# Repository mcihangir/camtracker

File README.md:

# SmartNFC

## Description
**SmartNFC** is an Android Virtual POS Application designed to operate on Android 13/14.

## Project Information
- **Project Name**: SmartNFC
- **Description**: Android Virtual POS Application
- **Start Date**: 2024-06-17
- **Firmware/SDK Version**: Android 13/14
- **Hardware Version**: v1.0

## Folder Structure
The project follows the directory structure outlined below:

```
SmartNFC/
│-- Block Diagrams/        # Product Block Diagram, PCB Connector Position
│-- Product Tree/          # Product Tree
│-- Documents/             # Design Documents, User Manuals, etc.
│-- Hardware/              # PCB Design Sources and libraries
│-- Software/              # Firmware and Applications
│-- Tools/                 # Software Tools
│-- Data/                  # Manufacturing data (PCB Gerber, Firmware Images, etc.)
```

## Folder Descriptions
- **Block Diagrams/**: Contains product-level block diagrams and PCB connector positioning.
- **Product Tree/**: Hierarchical structure of the product components.
- **Documents/**: Includes all necessary datasheets related to the hardware components and design documents.
- **Hardware/**: Contains PCB design source files and libraries.
- **Software/**: Includes firmware and application source code.
- **Tools/**: Collection of software tools required for development and debugging.
- **Data/**: Stores manufacturing data, including PCB Gerber files and firmware images.

## License
TBD

## Contact
For more details, reach out to the development team.

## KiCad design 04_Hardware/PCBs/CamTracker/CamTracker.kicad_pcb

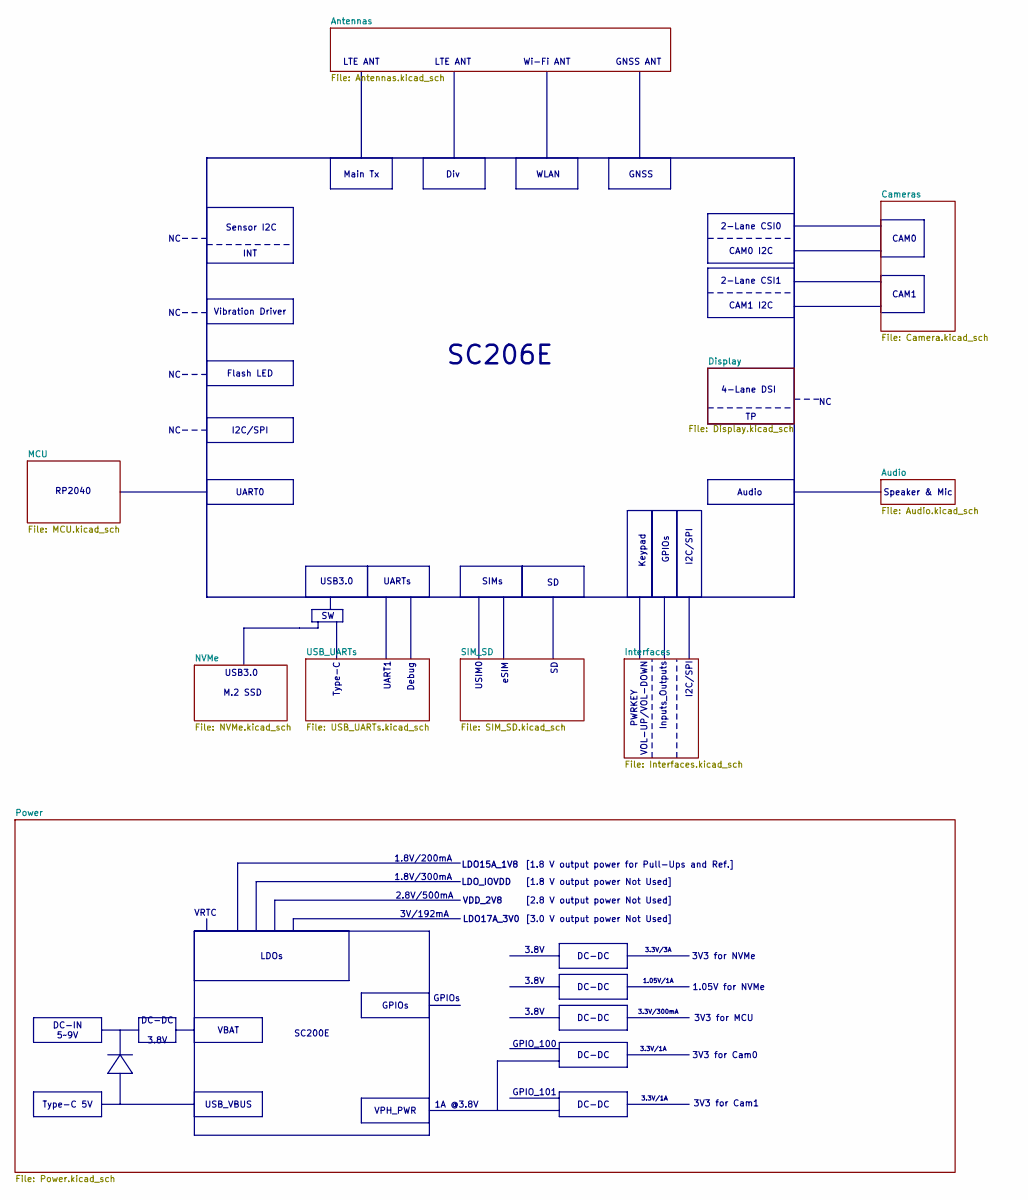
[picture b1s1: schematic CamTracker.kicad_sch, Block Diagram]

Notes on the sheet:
PWRKEY VOL-UP/VOL-DOWN
3V3 for MCU
LDO17A_3V0
UARTs
1.05V for NVMe
Debug
GPIOs
I2C/SPI
Inputs_Outputs
USIM0
3.8V
CAM1
[1.8 V output power Not Used]
[3.0 V output power Not Used]
RP2040
1.8V/300mA
1.05V/1A
4-Lane DSI
VRTC
3.3V/1A
3V3 for NVMe
3.8V
USB3.0
SC206E
1A @3.8V
Type-C
CAM0
eSIM
2.8V/500mA
Vibration Driver
3.3V/300mA
2-Lane CSI1
Main Tx
Speaker & Mic
3V3 for Cam0
M.2 SSD
GNSS
VDD_2V8
2-Lane CSI0
CAM1 I2C

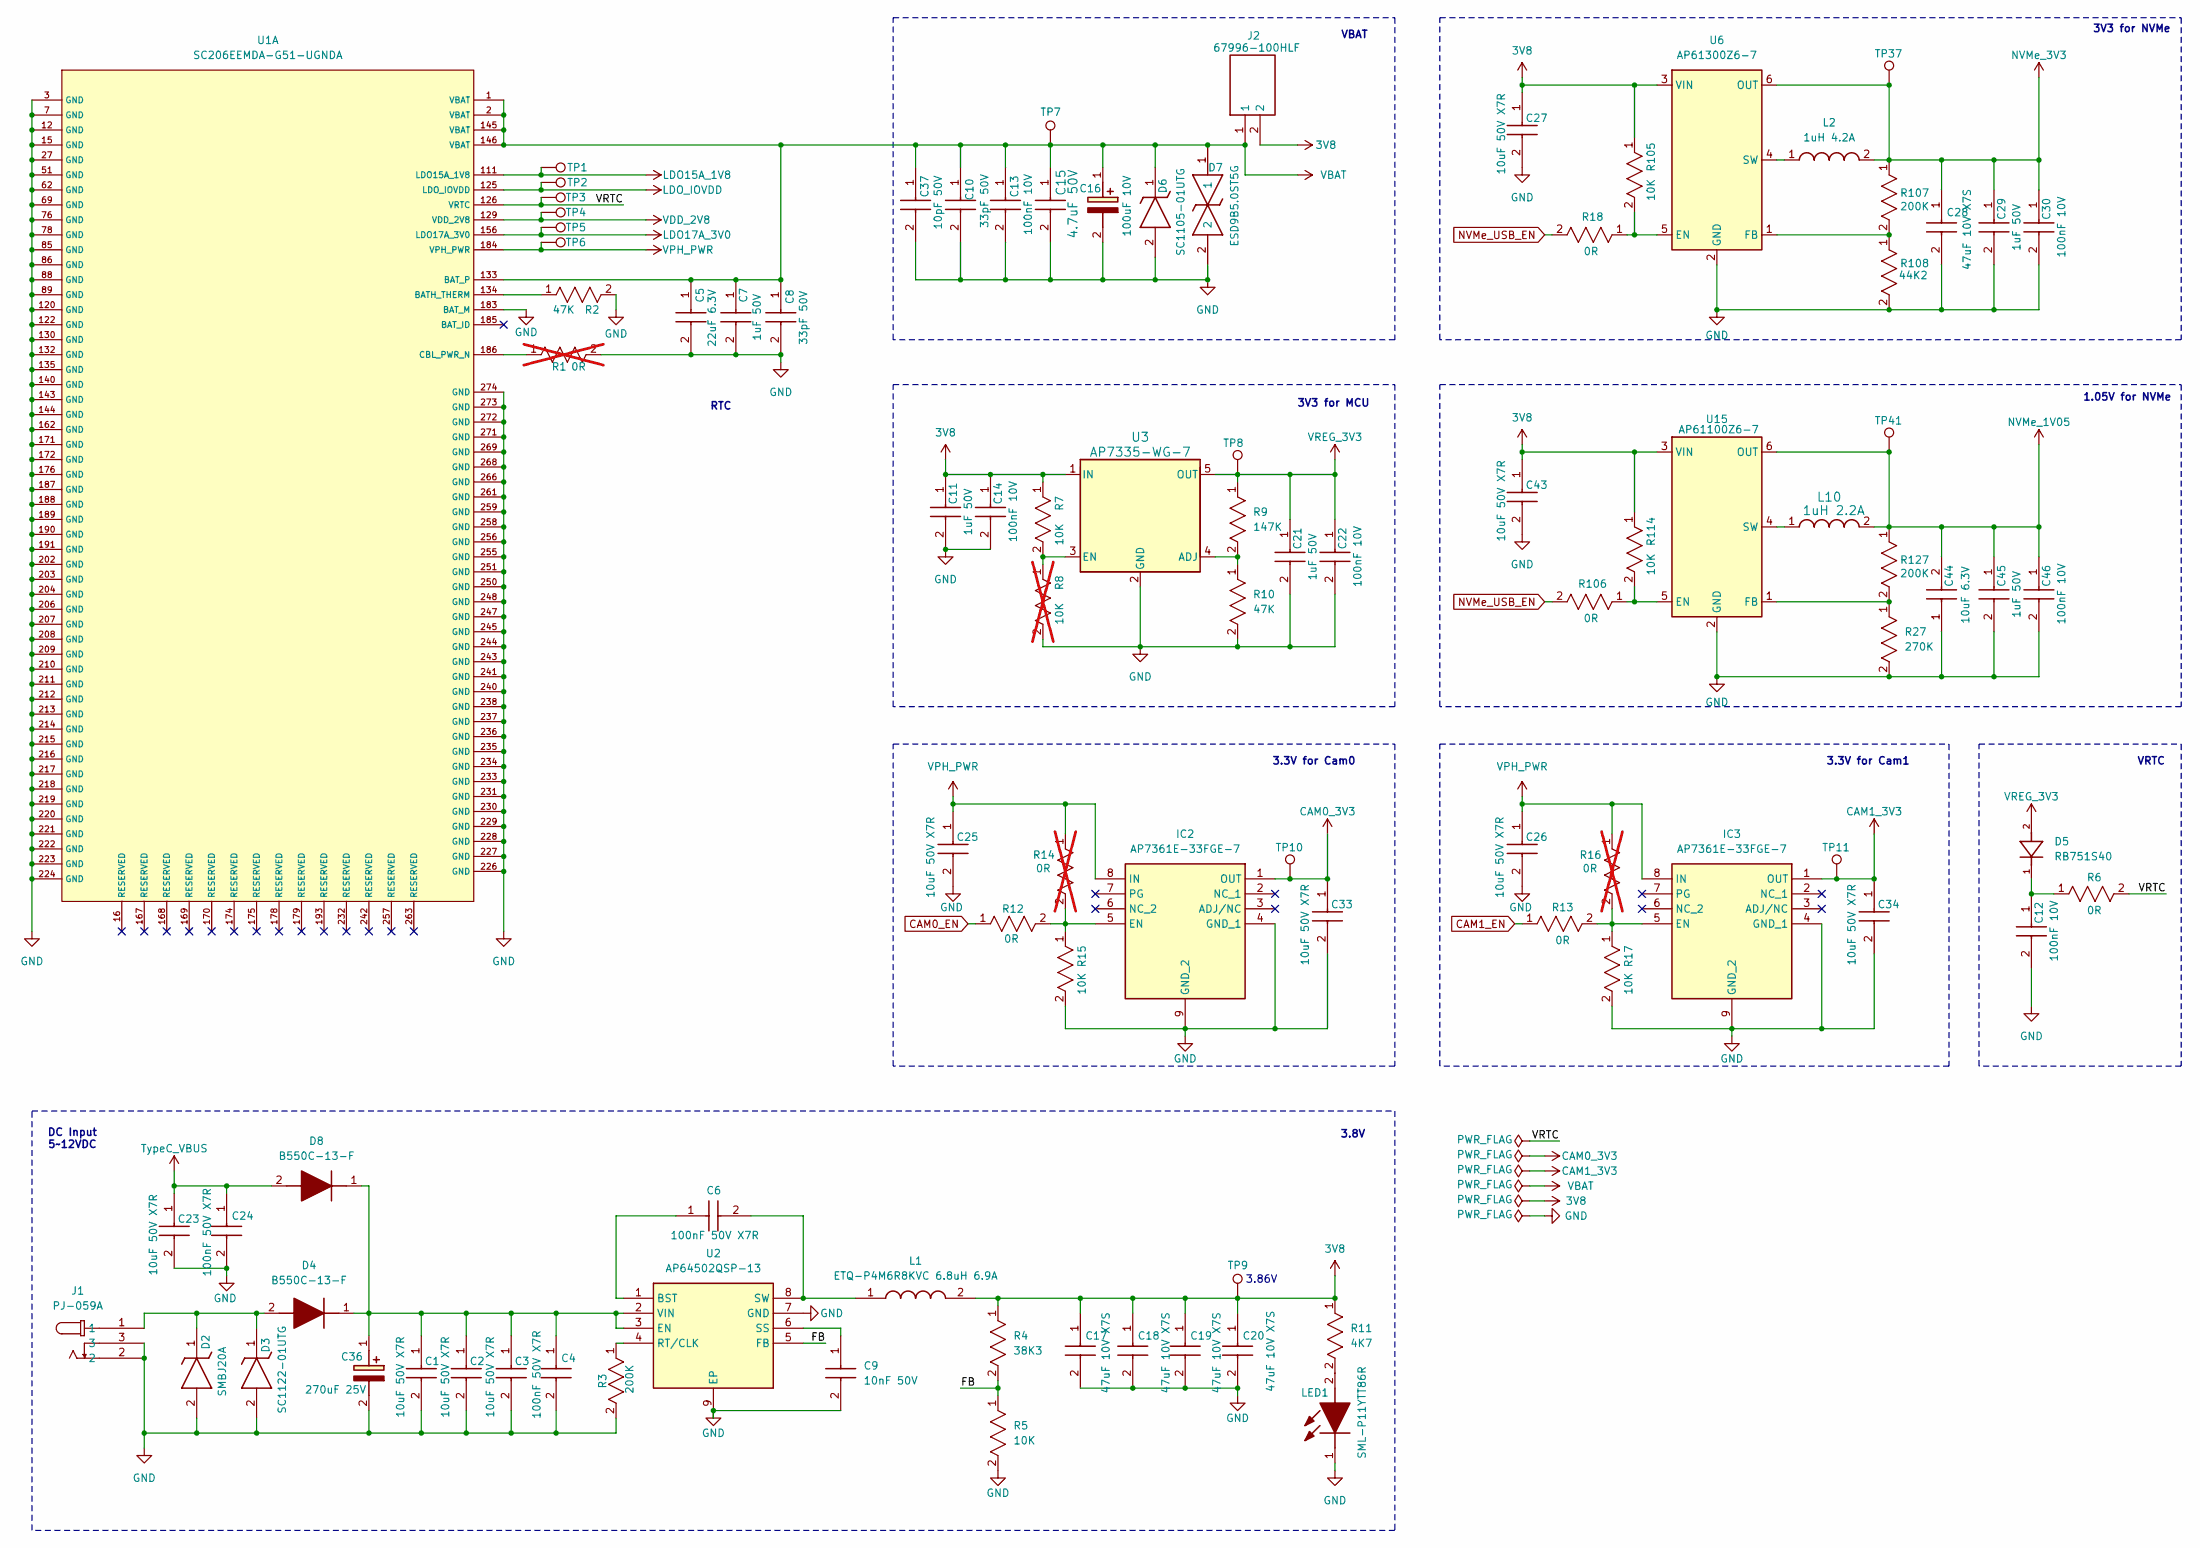
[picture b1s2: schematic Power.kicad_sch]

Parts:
C1, C2, C3, C23, C25, C26, C27, C33, C34, C43: 10uF 50V X7R; CAPC3216X190N; Part Number CL31B106KBK6PJE
C4, C6, C24: 100nF 50V X7R; CAPC1005X55N; Part Number UMK105B7104KVHF
C5: 22uF 6.3V; CAPC1005X55N; Part Number GRM158R60J226ME01D
C7, C11, C21, C29, C45: 1uF 50V; CAPC1005X55N; Part Number GRM155R61H105KE05D
C8, C10: 33pF 50V; CAPC1005X55N; Part Number GRM1555C1H330JA01D
C9: 10nF 50V; CAPC1005X55N; Part Number GRM155R71H103KA88D
C12, C13, C14, C22, C30, C46: 100nF 10V; CAPC1005X55N; Part Number GRM155R71A104KA01D
C15: 4.7uF 50V; CAP_UMK325B7475MM-T_TAY; Part Number UMK325BJ475MM-T
C16: 100uF 10V; T495D; Part Number T495D107K010ATE080
C17, C18, C19, C20, C28: 47uF 10V X7S; CAPC3225X280N; Part Number CGA6P1X7S1A476M250AC
C36: 270uF 25V; 16SVPT560M; Part Number 25SVPG270M
C37: 10pF 50V; CAPC1005X55N; Part Number GRM1555C1H100JA01D
C44: 10uF 6.3V; CAPC1005X55N; Part Number GRM155R60J106ME15D
D2: SMBJ20A; DIOM5436X244N; Part Number SMBJ20A
D3: SC1122-01UTG; SC110501UTG; Part Number SC1122-01UTG
D4, D8: B550C-13-F; DIOM7959X250N; Part Number B550C-13-F
D5: RB751S40; SOD1608X70; Part Number RB751S40
D6: SC1105-01UTG; SC110501UTG; Part Number SC1105-01UTG
D7: ESD9B5.0ST5G; SODFL1006X40N; Part Number ESD9B5.0ST5G
IC2, IC3: AP7361E-33FGE-7; SON65P300X300X63-9N; Part Number AP7361E-33FGE-7
J1: PJ-059A; PJ059A; Part Number PJ-059A
J2: 67996-100HLF; HDRV2W67P254_2X1_254X483X858P; Part Number 67996-100HLF
L1: ETQ-P4M6R8KVC 6.8uH 6.9A; ETQ-P4M_KVC; Part Number ETQ-P4M6R8KVC
L2: 1uH 4.2A; LSEUC3225HKT1R0M; Part Number LSEUC3225HKT1R0M
L10: 1uH 2.2A; IND_WE-LQS_2512_WRE; Part Number 74404024010
LED1: SML-P11YTT86R; SMLP11VTT86R; Part Number SML-P11YTT86R
R1: 0R; RC0402N_YAG; Part Number RC0402JR-070RL; not fitted
R2, R10: 47K; RC0402N_YAG; Part Number RC0402JR-0747KL
R3, R107, R127: 200K; RC0402N_YAG; Part Number RC0402FR-07200KL
R4: 38K3; RC0402N_YAG; Part Number AF0402FR-0738K3L
R5, R7, R15, R17, R105, R114: 10K; RC0402N_YAG; Part Number RC0402JR-0710KL
R6, R12, R13: 0R; RESC2012X50N; Part Number CRCW08050000Z0EA
R8: 10K; RC0402N_YAG; Part Number RC0402JR-0710KL; not fitted
R9: 147K; RC0402N_YAG; Part Number RC0402FR-07147KL
R11: 4K7; RC0402N_YAG; Part Number RC0402JR-074K7L
R14, R16: 0R; RESC2012X50N; Part Number CRCW08050000Z0EA; not fitted
R18, R106: 0R; RC0402N_YAG; Part Number RC0402JR-070RL
R27: 270K; RC0402N_YAG; Part Number RC0402FR-07270KL
R108: 44K2; RC0402N_YAG; Part Number RC0402FR-0744K2L
TP1, TP2, TP3, TP4, TP5, TP6, TP7, TP8, TP10, TP11, TP37, TP41: TestPoint; TestPoint_Pad_D1.0mm
TP9: 3.86V; TestPoint_Pad_D1.0mm
U1: SC206EEMDA-G51-UGNDA; SC200E_SC206E; Part Number SC200EEMNA-E53-UGNDA
U2: AP64502QSP-13; SOIC127P600X163-9N; Part Number AP64502QSP-13
U3: AP7335-WG-7; SOT95P285X145-5N; Part Number AP7335-WG-7
U6: AP61300Z6-7; SOT50P162X60-6N; Part Number AP61100Z6-7
U15: AP61100Z6-7; SOT50P162X60-6N; Part Number AP61100Z6-7

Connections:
3V8: C11.1, C14.1, C17.1, C18.1, C19.1, C20.1, C27.1, C43.1, J2.2, L1.2, R4.1, R7.1, R11.1, R105.1, R114.1, TP9.1, U3.1 (IN), U6.3 (VIN), U15.3 (VIN); also elsewhere on the board
/Power/FB: R4.2, R5.1, U2.5 (FB)
/Power/VRTC: R6.2, TP3.1, U1.126 (VRTC)
CAM0_3V3: C33.1, IC2.1 (OUT), TP10.1; also elsewhere on the board
CAM0_EN: R12.1; also elsewhere on the board
CAM1_3V3: C34.1, IC3.1 (OUT), TP11.1; also elsewhere on the board
CAM1_EN: R13.1; also elsewhere on the board
GND: C1.2, C2.2, C3.2, C4.2, C5.2, C7.2, C8.2, C9.2, C10.2, C11.2, C12.2, C13.2, C14.2, C15.2, C16.2 (-), C17.2, C18.2, C19.2, C20.2, C21.2, C22.2, C23.2, C24.2, C25.2, C26.2, C27.2, C28.2, C29.2, C30.2, C33.2, C34.2, C36.2 (-), C37.2, C43.2, C44.1, C45.2, C46.2, D2.2 (A), D3.2 (A), D6.2 (A), D7.2, IC2.4 (GND_1), IC2.9 (GND_2), IC3.4 (GND_1), IC3.9 (GND_2), J1.2, J1.3, LED1.1 (K), R1.2, R2.2, R3.2, R5.2, R8.2, R10.2, R15.2, R17.2, R27.2, R108.2, U1.3 (GND), U1.7 (GND), U1.12 (GND), U1.15 (GND), U1.27 (GND), U1.51 (GND), U1.62 (GND), U1.69 (GND), U1.76 (GND), U1.78 (GND), U1.85 (GND), U1.86 (GND), U1.88 (GND), U1.89 (GND), U1.120 (GND), U1.122 (GND), U1.130 (GND), U1.132 (GND), U1.135 (GND), U1.140 (GND), U1.143 (GND), U1.144 (GND), U1.162 (GND), U1.171 (GND), U1.172 (GND), U1.176 (GND), U1.183 (BAT_M), U1.187 (GND), U1.188 (GND), U1.189 (GND), U1.190 (GND), U1.191 (GND), U1.202 (GND), U1.203 (GND), U1.204 (GND), U1.206 (GND), U1.207 (GND), U1.208 (GND), U1.209 (GND), U1.210 (GND), U1.211 (GND), U1.212 (GND), U1.213 (GND), U1.214 (GND), U1.215 (GND), U1.216 (GND), U1.217 (GND), U1.218 (GND), U1.219 (GND), U1.220 (GND), U1.221 (GND), U1.222 (GND), U1.223 (GND), U1.224 (GND), U1.226 (GND), U1.227 (GND), U1.228 (GND), U1.229 (GND), U1.230 (GND), U1.231 (GND), U1.233 (GND), U1.234 (GND), U1.235 (GND), U1.236 (GND), U1.237 (GND), U1.238 (GND), U1.240 (GND), U1.241 (GND), U1.243 (GND), U1.244 (GND), U1.245 (GND), U1.247 (GND), U1.248 (GND), U1.250 (GND), U1.251 (GND), U1.255 (GND), U1.256 (GND), U1.258 (GND), U1.259 (GND), U1.261 (GND), U1.266 (GND), U1.268 (GND), U1.269 (GND), U1.271 (GND), U1.272 (GND), U1.273 (GND), U1.274 (GND), U2.7 (GND), U2.9 (EP), U3.2 (GND), U6.2 (GND), U15.2 (GND); also elsewhere on the board
LDO15A_1V8: TP1.1, U1.111 (LDO15A_1V8); also elsewhere on the board
LDO17A_3V0: TP5.1, U1.156 (LDO17A_3V0)
LDO_IOVDD: TP2.1, U1.125 (LDO_IOVDD)
NVMe_1V05: C44.2, C45.1, C46.1, L10.2, R127.1, TP41.1, U15.6 (OUT); also elsewhere on the board
NVMe_3V3: C28.1, C29.1, C30.1, L2.2, R107.1, TP37.1, U6.6 (OUT); also elsewhere on the board
NVMe_USB_EN: R18.2, R106.2; also elsewhere on the board
unnamed: C12.1, D5.1, R6.1
unnamed: C1.1, C2.1, C3.1, C4.1, C36.1 (+), D4.1 (K), D8.1 (K), U2.2 (VIN), U2.3 (EN)
unnamed: D2.1 (K), D3.1 (K), D4.2 (A), J1.1
unnamed: IC2.5 (EN), R12.2, R14.2, R15.1
unnamed: IC3.5 (EN), R13.2, R16.2, R17.1
unnamed: LED1.2 (A), R11.2
unnamed: R2.1, U1.134 (BATH_THERM)
unnamed: R1.1, U1.186 (CBL_PWR_N)
unnamed: C6.1, U2.1 (BST)
unnamed: R3.1, U2.4 (RT/CLK)
unnamed: C9.1, U2.6 (SS)
unnamed: C6.2, L1.1, U2.8 (SW)
unnamed: R9.2, R10.1, U3.4 (ADJ)
unnamed: R7.2, R8.1, U3.3 (EN)
unnamed: R18.1, R105.2, U6.5 (EN)
unnamed: R107.2, R108.1, U6.1 (FB)
unnamed: L2.1, U6.4 (SW)
unnamed: R106.1, R114.2, U15.5 (EN)
unnamed: R27.1, R127.2, U15.1 (FB)
unnamed: L10.1, U15.4 (SW)
TypeC_VBUS: C23.1, C24.1, D8.2 (A); also elsewhere on the board
VBAT: C5.1, C7.1, C8.1, C10.1, C13.1, C15.1, C16.1 (+), C37.1, D6.1 (K), D7.1, J2.1, TP7.1, U1.1 (VBAT), U1.2 (VBAT), U1.133 (BAT_P), U1.145 (VBAT), U1.146 (VBAT); also elsewhere on the board
VDD_2V8: TP4.1, U1.129 (VDD_2V8)
VPH_PWR: C25.1, C26.1, IC2.8 (IN), IC3.8 (IN), R14.1, R16.1, TP6.1, U1.184 (VPH_PWR); also elsewhere on the board
VREG_3V3: C21.1, C22.1, D5.2, R9.1, TP8.1, U3.5 (OUT); also elsewhere on the board

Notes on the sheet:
3.3V for Cam0
VBAT
1.05V for NVMe
3V3 for NVMe
3V3 for MCU
RTC
3.8V
DC Input 5~12VDC
3.3V for Cam1
3.86V
VRTC

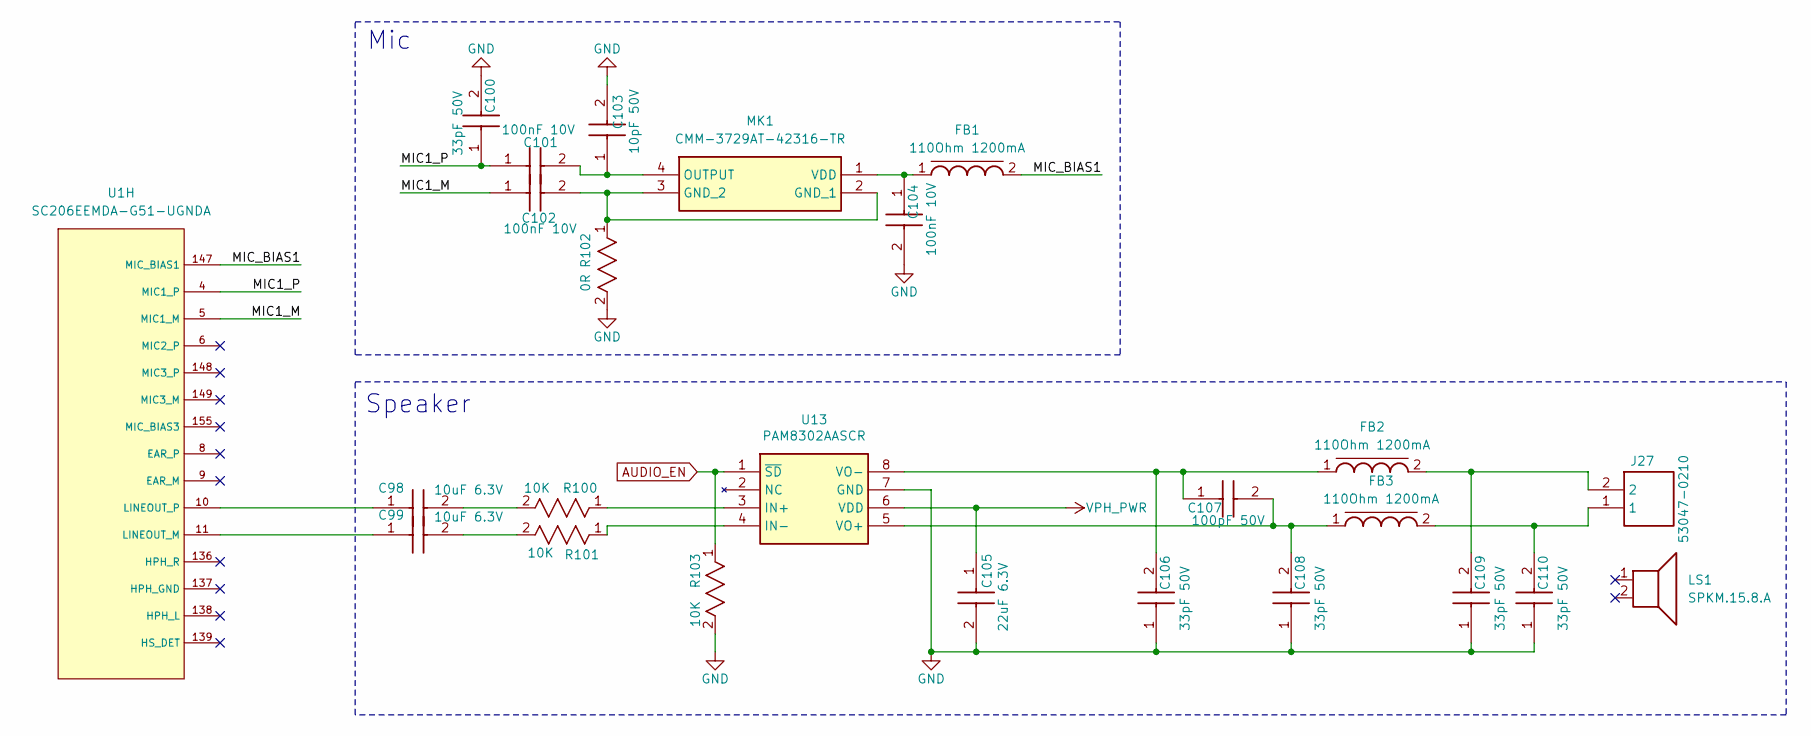
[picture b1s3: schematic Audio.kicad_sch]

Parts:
C98, C99: 10uF 6.3V; CAPC1005X55N; Part Number GRM155R60J106ME15D
C100, C106, C108, C109, C110: 33pF 50V; CAPC1005X55N; Part Number GRM1555C1H330JA01D
C101, C102, C104: 100nF 10V; CAPC1005X55N; Part Number GRM155R71A104KA01D
C103: 10pF 50V; CAPC1005X55N; Part Number GRM1555C1H100JA01D
C105: 22uF 6.3V; CAPC1005X55N; Part Number GRM158R60J226ME01D
C107: 100pF 50V; CAPC1005X55N; Part Number GRM1555C1H101JA01J
FB1, FB2, FB3: 110Ohm 1200mA; BEADC1005X55N; Part Number 74269242111
J27: 53047-0210; 530470210; Part Number 53047-0210
LS1: SPKM.15.8.A; Part Number SPKM.15.8.A
MK1: CMM-3729AT-42316-TR; CMM3729AT42316TR; Part Number CMM-3729AT-42316-TR
R100, R101, R103: 10K; RC0402N_YAG; Part Number RC0402JR-0710KL
R102: 0R; RC0402N_YAG; Part Number RC0402JR-070RL
U1: SC206EEMDA-G51-UGNDA; SC200E_SC206E; Part Number SC200EEMNA-E53-UGNDA
U13: PAM8302AASCR; SOP65P490X110-8N; Part Number PAM8302AASCR

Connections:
/Audio/MIC1_M: C102.1, U1.5 (MIC1_M)
/Audio/MIC1_P: C100.1, C101.1, U1.4 (MIC1_P)
/Audio/MIC_BIAS1: FB1.2, U1.147 (MIC_BIAS1)
AUDIO_EN: R103.1, U13.1 (~SD); also elsewhere on the board
GND: C100.2, C103.2, C104.2, C105.2, C106.1, C108.1, C109.1, C110.1, R102.2, R103.2, U13.7 (GND); also elsewhere on the board
unnamed: C98.2, R100.2
unnamed: C99.2, R101.2
unnamed: C109.2, FB2.2, J27.2
unnamed: C110.2, FB3.2, J27.1
unnamed: C102.2, MK1.2 (GND_1), MK1.3 (GND_2), R102.1
unnamed: C101.2, C103.1, MK1.4 (OUTPUT)
unnamed: C104.1, FB1.1, MK1.1 (VDD)
unnamed: C99.1, U1.11 (LINEOUT_M)
unnamed: C98.1, U1.10 (LINEOUT_P)
unnamed: R100.1, U13.3 (IN+)
unnamed: R101.1, U13.4 (IN-)
unnamed: C107.2, C108.2, FB3.1, U13.5 (VO+)
unnamed: C106.2, C107.1, FB2.1, U13.8 (VO-)
VPH_PWR: C105.1, U13.6 (VDD); also elsewhere on the board

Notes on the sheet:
Mic
Speaker

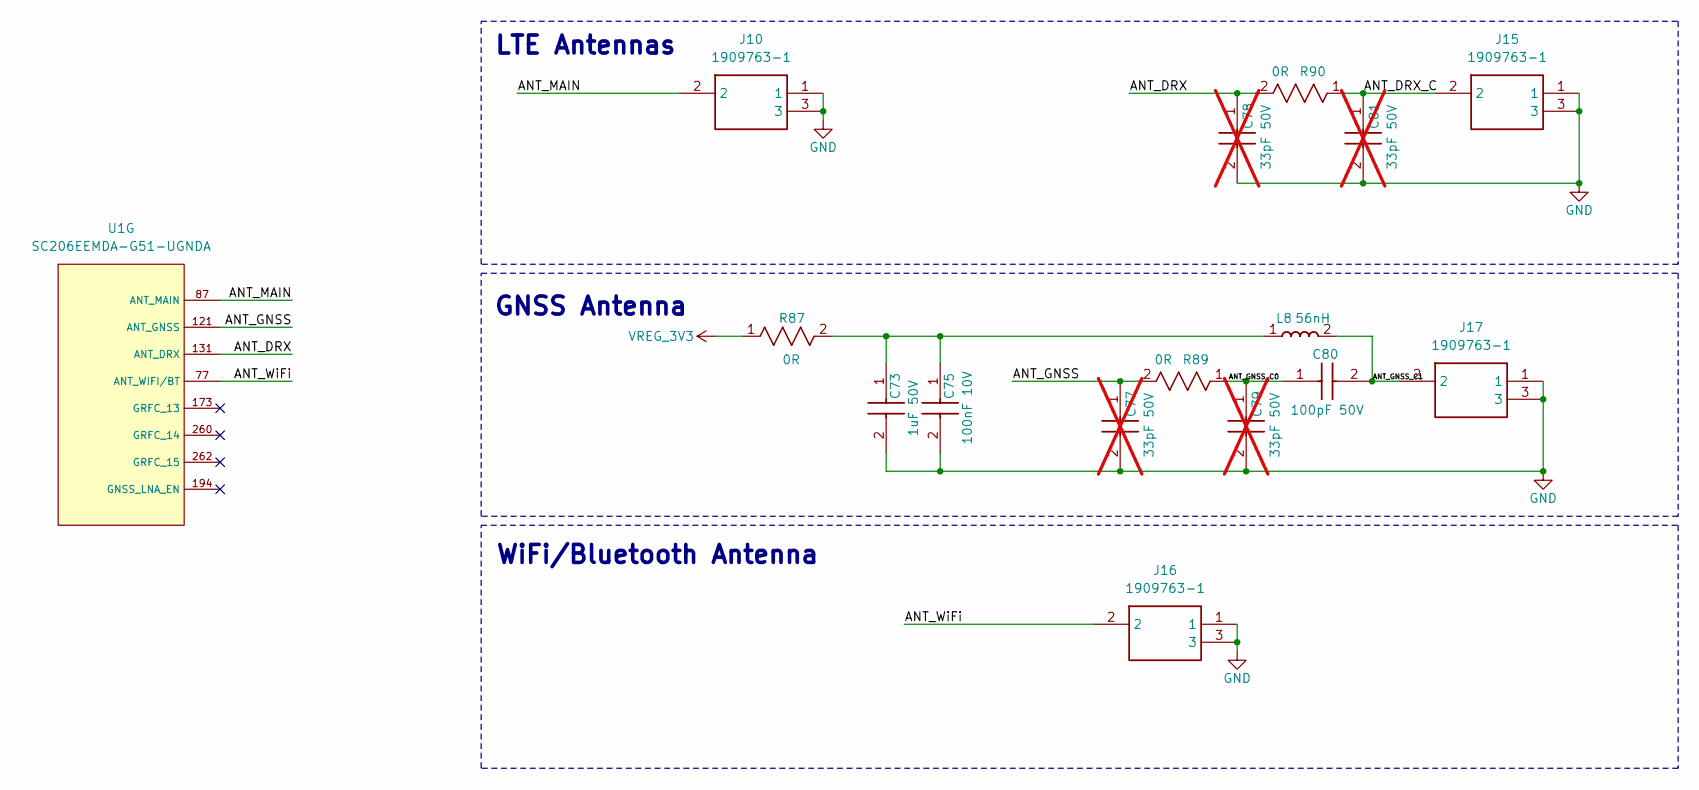
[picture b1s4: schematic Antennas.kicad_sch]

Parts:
C73: 1uF 50V; CAPC1005X55N; Part Number GRM155R61H105KE05D
C75: 100nF 10V; CAPC1005X55N; Part Number GRM155R71A104KA01D
C77, C78, C79, C81: 33pF 50V; CAPC1005X55N; Part Number GRM1555C1H330JA01D; not fitted
C80: 100pF 50V; CAPC1005X55N; Part Number GRM1555C1H101JA01J
J10, J15, J16, J17: 1909763-1; Part Number 1909763-1
L8: 56nH; INDC1005X60N; Part Number 744784156A
R87: 0R; RESC2012X50N; Part Number CRCW08050000Z0EA
R89, R90: 0R; RC0402N_YAG; Part Number RC0402JR-070RL
U1: SC206EEMDA-G51-UGNDA; SC200E_SC206E; Part Number SC200EEMNA-E53-UGNDA

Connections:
/Antennas/ANT_DRX: C78.1, R90.2, U1.131 (ANT_DRX)
/Antennas/ANT_DRX_C: C81.1, J15.2, R90.1
/Antennas/ANT_GNSS: C77.1, R89.2, U1.121 (ANT_GNSS)
/Antennas/ANT_GNSS_C0: C79.1, C80.1, R89.1
/Antennas/ANT_GNSS_C1: C80.2, J17.2, L8.2
/Antennas/ANT_MAIN: J10.2, U1.87 (ANT_MAIN)
/Antennas/ANT_WiFi: J16.2, U1.77 (ANT_WIFI/BT)
GND: C73.2, C75.2, C77.2, C78.2, C79.2, C81.2, J10.1, J10.3, J15.1, J15.3, J16.1, J16.3, J17.1, J17.3; also elsewhere on the board
unnamed: C73.1, C75.1, L8.1, R87.2
VREG_3V3: R87.1; also elsewhere on the board

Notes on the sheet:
WiFi/Bluetooth Antenna
LTE Antennas
GNSS Antenna

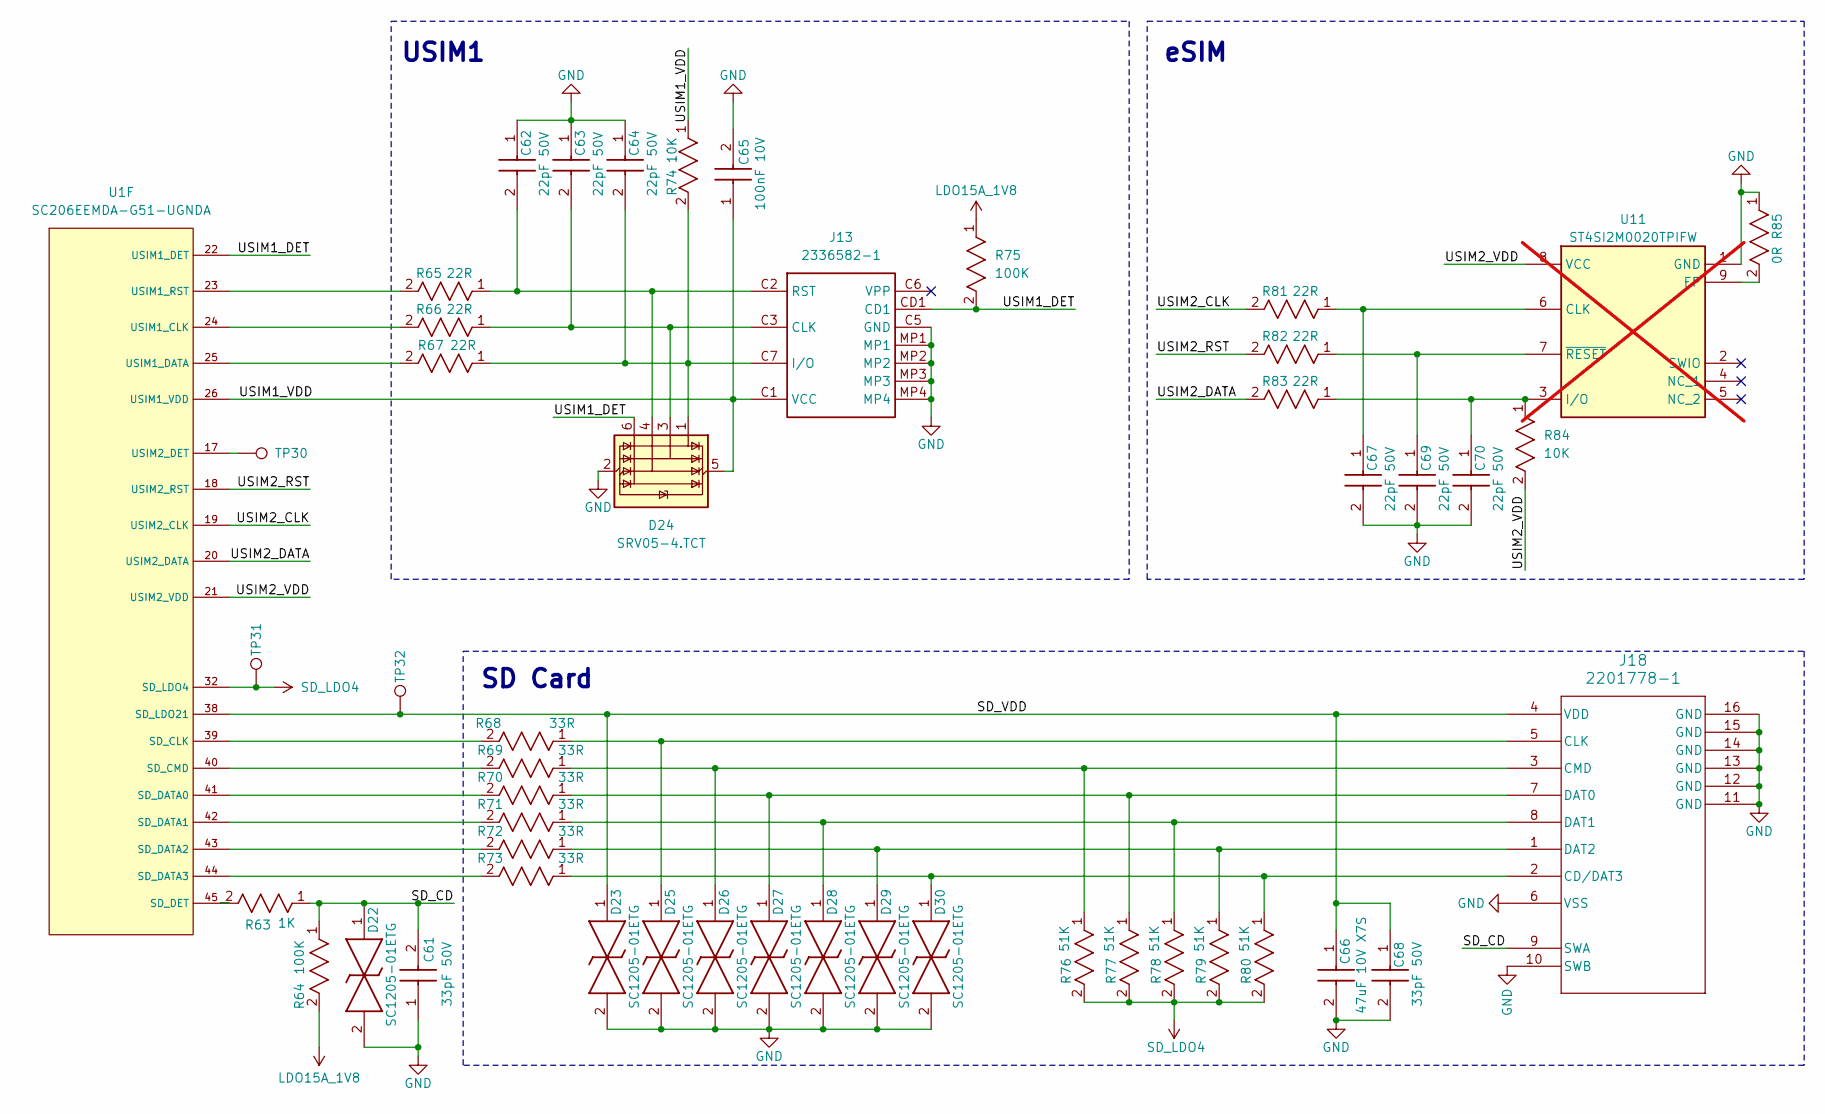
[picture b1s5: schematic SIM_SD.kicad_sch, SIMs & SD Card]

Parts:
C61, C68: 33pF 50V; CAPC1005X55N; Part Number GRM1555C1H330JA01D
C62, C63, C64, C67, C69, C70: 22pF 50V; CAPC1005X55N; Part Number GRM1555C1H220JA01D
C65: 100nF 10V; CAPC1005X55N; Part Number GRM155R71A104KA01D
C66: 47uF 10V X7S; CAPC3225X280N; Part Number CGA6P1X7S1A476M250AC
D22, D23, D25, D26, D27, D28, D29, D30: SC1205-01ETG; SC120501ETG; Part Number SC1205-01ETG
D24: SRV05-4.TCT; SOT95P280X145-6N; Part Number SRV05-4.TCT
J13: 2336582-1; 23365821; Part Number 2336582-1
J18: 2201778-1; 2201778-1_TEC; Part Number 2201778-1
R63: 1K; RC0402N_YAG; Part Number RC0402JR-071KL
R64, R75: 100K; RC0402N_YAG; Part Number RC0402JR-07100KL
R65, R66, R67, R81, R82, R83: 22R; RC0402N_YAG; Part Number RC0402JR-0722RL
R68, R69, R70, R71, R72, R73: 33R; RC0402N_YAG; Part Number RC0402JR-0733RL
R74, R84: 10K; RC0402N_YAG; Part Number RC0402JR-0710KL
R76, R77, R78, R79, R80: 51K; RC0402N_YAG; Part Number RC0402JR-0751KL
R85: 0R; RC0402N_YAG; Part Number RC0402JR-070RL
TP30, TP31, TP32: TestPoint; TestPoint_Pad_D1.0mm
U1: SC206EEMDA-G51-UGNDA; SC200E_SC206E; Part Number SC200EEMNA-E53-UGNDA
U11: ST4SI2M0020TPIFW; SON127P600X500X100-9N; Part Number ST4SI2M0020TPIFW; not fitted

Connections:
/SIM_SD/SD_CD: C61.2, D22.1, J18.9 (SWA), R63.1, R64.1
/SIM_SD/SD_VDD: C66.1, C68.1, D23.1, J18.4 (VDD), TP32.1, U1.38 (SD_LDO21)
/SIM_SD/USIM1_DET: D24.6 (I/O4), J13.CD1, R75.2, U1.22 (USIM1_DET)
/SIM_SD/USIM1_VDD: C65.1, D24.5 (VBUS), J13.C1 (VCC), R74.1, U1.26 (USIM1_VDD)
/SIM_SD/USIM2_CLK: R81.2, U1.19 (USIM2_CLK)
/SIM_SD/USIM2_DATA: R83.2, U1.20 (USIM2_DATA)
/SIM_SD/USIM2_RST: R82.2, U1.18 (USIM2_RST)
/SIM_SD/USIM2_VDD: R84.2, U1.21 (USIM2_VDD), U11.8 (VCC)
GND: C61.1, C62.1, C63.1, C64.1, C65.2, C66.2, C67.2, C68.2, C69.2, C70.2, D22.2, D23.2, D24.2 (GND), D25.2, D26.2, D27.2, D28.2, D29.2, D30.2, J13.C5 (GND), J13.MP1, J13.MP2, J13.MP3, J13.MP4, J18.6 (VSS), J18.10 (SWB), J18.11 (GND), J18.12 (GND), J18.13 (GND), J18.14 (GND), J18.15 (GND), J18.16 (GND), R85.1, U11.1 (GND); also elsewhere on the board
LDO15A_1V8: R64.2, R75.1; also elsewhere on the board
unnamed: C64.2, D24.1 (I/O1), J13.C7 (I/O), R67.1, R74.2
unnamed: C63.2, D24.3 (I/O2), J13.C3 (CLK), R66.1
unnamed: C62.2, D24.4 (I/O3), J13.C2 (RST), R65.1
unnamed: D30.1, J18.2 (CD/DAT3), R73.1, R80.1
unnamed: D25.1, J18.5 (CLK), R68.1
unnamed: D26.1, J18.3 (CMD), R69.1, R76.1
unnamed: D27.1, J18.7 (DAT0), R70.1, R77.1
unnamed: D28.1, J18.8 (DAT1), R71.1, R78.1
unnamed: D29.1, J18.1 (DAT2), R72.1, R79.1
unnamed: R68.2, U1.39 (SD_CLK)
unnamed: R69.2, U1.40 (SD_CMD)
unnamed: R70.2, U1.41 (SD_DATA0)
unnamed: R71.2, U1.42 (SD_DATA1)
unnamed: R72.2, U1.43 (SD_DATA2)
unnamed: R73.2, U1.44 (SD_DATA3)
unnamed: R63.2, U1.45 (SD_DET)
unnamed: R66.2, U1.24 (USIM1_CLK)
unnamed: R67.2, U1.25 (USIM1_DATA)
unnamed: R65.2, U1.23 (USIM1_RST)
unnamed: TP30.1, U1.17 (USIM2_DET)
unnamed: C67.1, R81.1, U11.6 (CLK)
unnamed: R85.2, U11.9 (EP)
unnamed: C70.1, R83.1, R84.1, U11.3 (I/O)
unnamed: C69.1, R82.1, U11.7 (~RESET)
SD_LDO4: R76.2, R77.2, R78.2, R79.2, R80.2, TP31.1, U1.32 (SD_LDO4)

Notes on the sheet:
eSIM
USIM1
SD Card
